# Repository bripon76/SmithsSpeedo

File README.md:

# SmithsSpeedo
 DIY Speedo Conversation from mechanical to electical

# ToDo

- Control and order Top PCB
- Complete, control and order Bottom PCB
- modify Atmel Code for speaking with ESP32 Code

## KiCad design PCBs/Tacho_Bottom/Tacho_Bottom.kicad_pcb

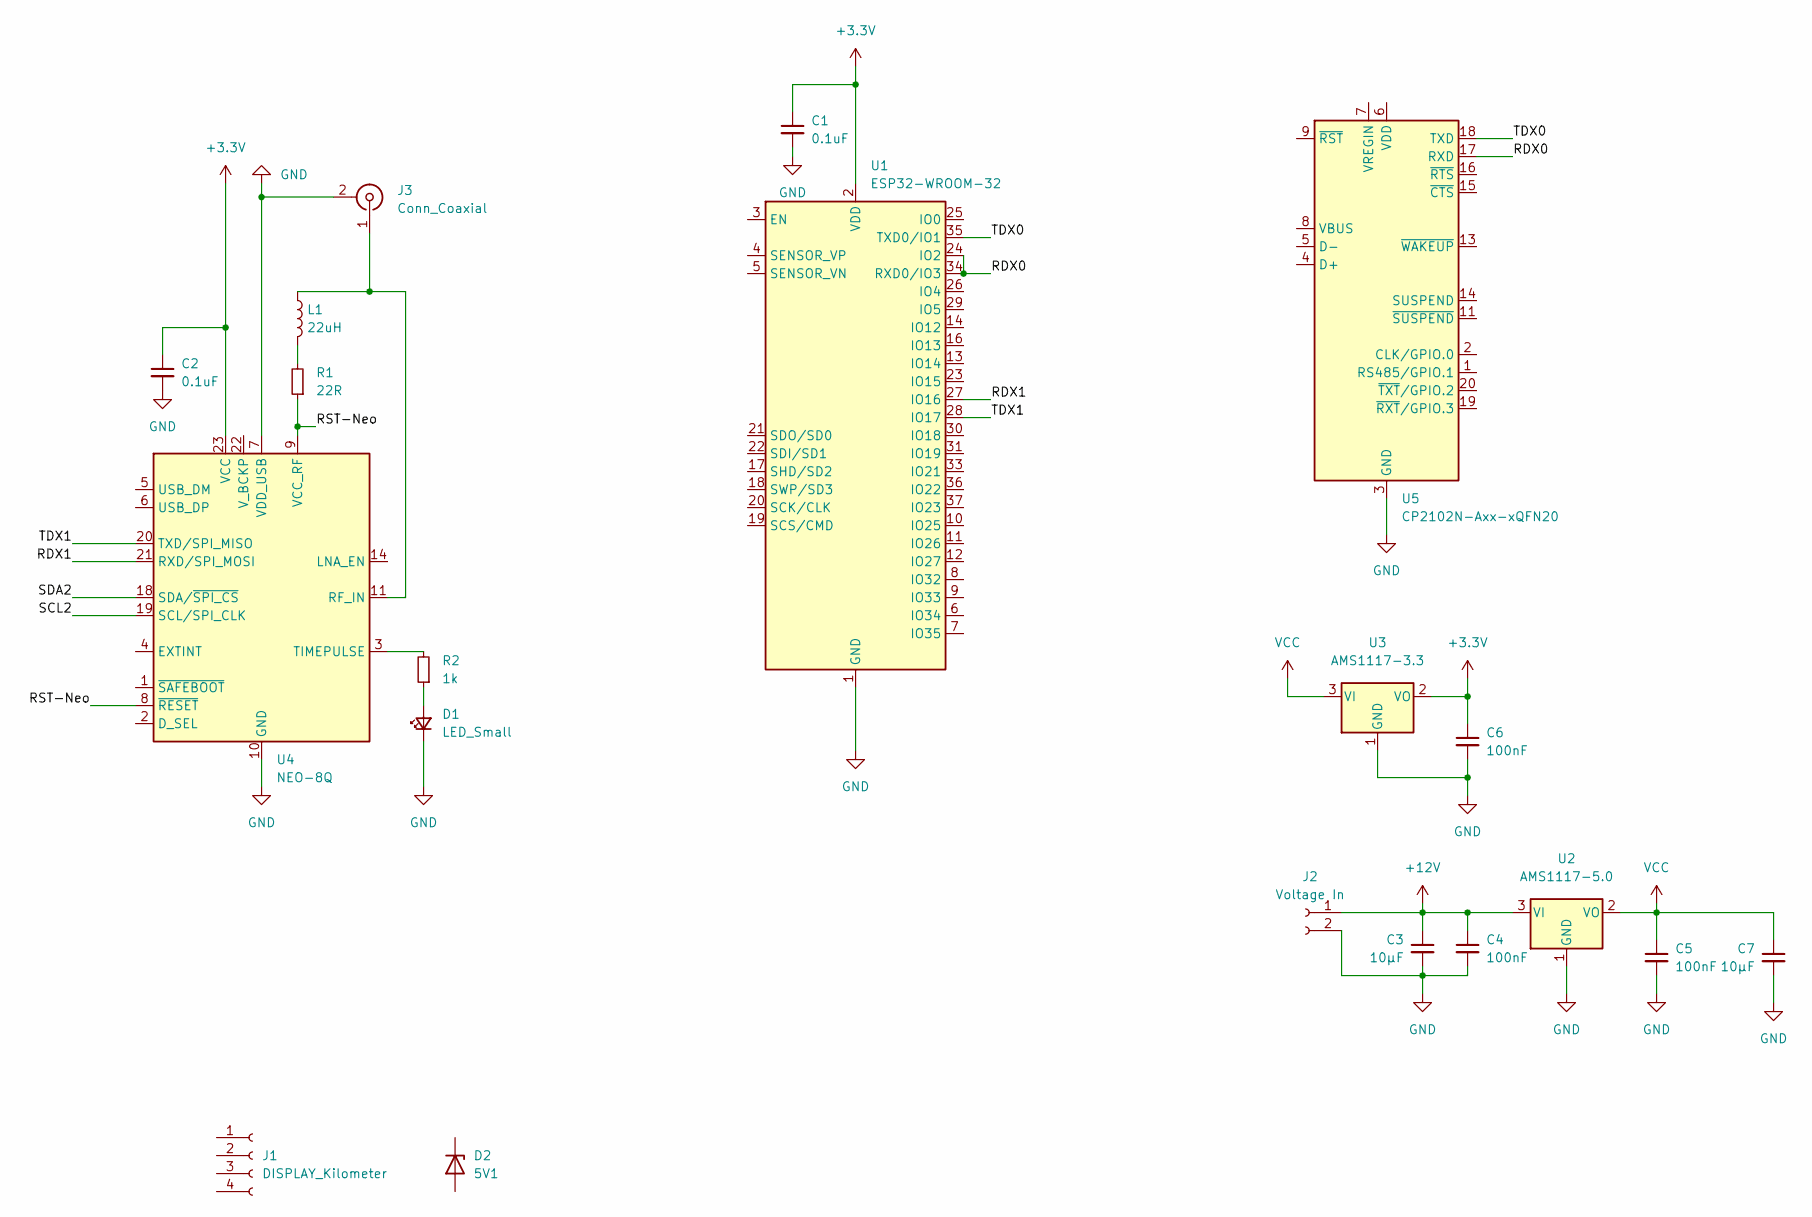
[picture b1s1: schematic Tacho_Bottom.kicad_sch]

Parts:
C1, C2: 0.1uF; C_0603_1608Metric_Pad1.08x0.95mm_HandSolder
C3, C7: 10µF; C_0805_2012Metric_Pad1.18x1.45mm_HandSolder
C4, C5, C6: 100nF; C_0603_1608Metric_Pad1.08x0.95mm_HandSolder
D1: LED_Small; LED_1206_3216Metric_Pad1.42x1.75mm_HandSolder
D2: 5V1; D_SOD-123
J1: DISPLAY_Kilometer; PinHeader_1x04_P2.54mm_Vertical
J2: Voltage In; SolderWire-0.5sqmm_1x02_P4.8mm_D0.9mm_OD2.3mm
J3: Conn_Coaxial; U.FL_Molex_MCRF_73412-0110_Vertical
L1: 22uH; L_12x12mm_H8mm
R1: 22R; R_0603_1608Metric_Pad0.98x0.95mm_HandSolder
R2: 1k; R_0603_1608Metric_Pad0.98x0.95mm_HandSolder
U1: ESP32-WROOM-32
U2: AMS1117-5.0; SOT-223-3_TabPin2
U3: AMS1117-3.3; SOT-223-3_TabPin2
U4: NEO-8Q; ublox_NEO
U5: CP2102N-Axx-xQFN20; SiliconLabs_QFN-20-1EP_3x3mm_P0.5mm

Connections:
+3.3V: C1.1, C2.1, C6.1, U1.2 (VDD), U3.2 (VO), U4.23 (VCC)
+12V: C3.1, C4.1, J2.1, U2.3 (VI)
/RDX0: U1.24 (IO2), U1.34 (RXD0/IO3), U5.17 (RXD)
/RDX1: U1.27 (IO16), U4.21 (RXD/SPI_MOSI)
/RST-Neo: R1.1, U4.8 (~RESET), U4.9 (VCC_RF)
/SCL2: U4.19 (SCL/SPI_CLK)
/SDA2: U4.18 (SDA/~SPI_CS)
/TDX0: U1.35 (TXD0/IO1), U5.18 (TXD)
/TDX1: U1.28 (IO17), U4.20 (TXD/SPI_MISO)
GND: C1.2, C2.2, C3.2, C4.2, C5.2, C6.2, C7.2, D1.1 (K), J2.2, J3.2 (Ext), U1.1 (GND), U1.15 (GND), U1.38 (GND), U1.39 (GND), U2.1 (GND), U3.1 (GND), U4.7 (VDD_USB), U4.10 (GND), U4.12 (GND), U4.13 (GND), U4.24 (GND), U5.3 (GND), U5.12 (GND), U5.21 (GND)
unnamed: D1.2 (A), R2.1
unnamed: J3.1 (In), L1.1, U4.11 (RF_IN)
unnamed: L1.2, R1.2
unnamed: R2.2, U4.3 (TIMEPULSE)
VCC: C5.1, C7.1, U2.2 (VO), U3.3 (VI)

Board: 2 copper layers, 19 parts (2 on the bottom side), 12 nets, no tracks yet.

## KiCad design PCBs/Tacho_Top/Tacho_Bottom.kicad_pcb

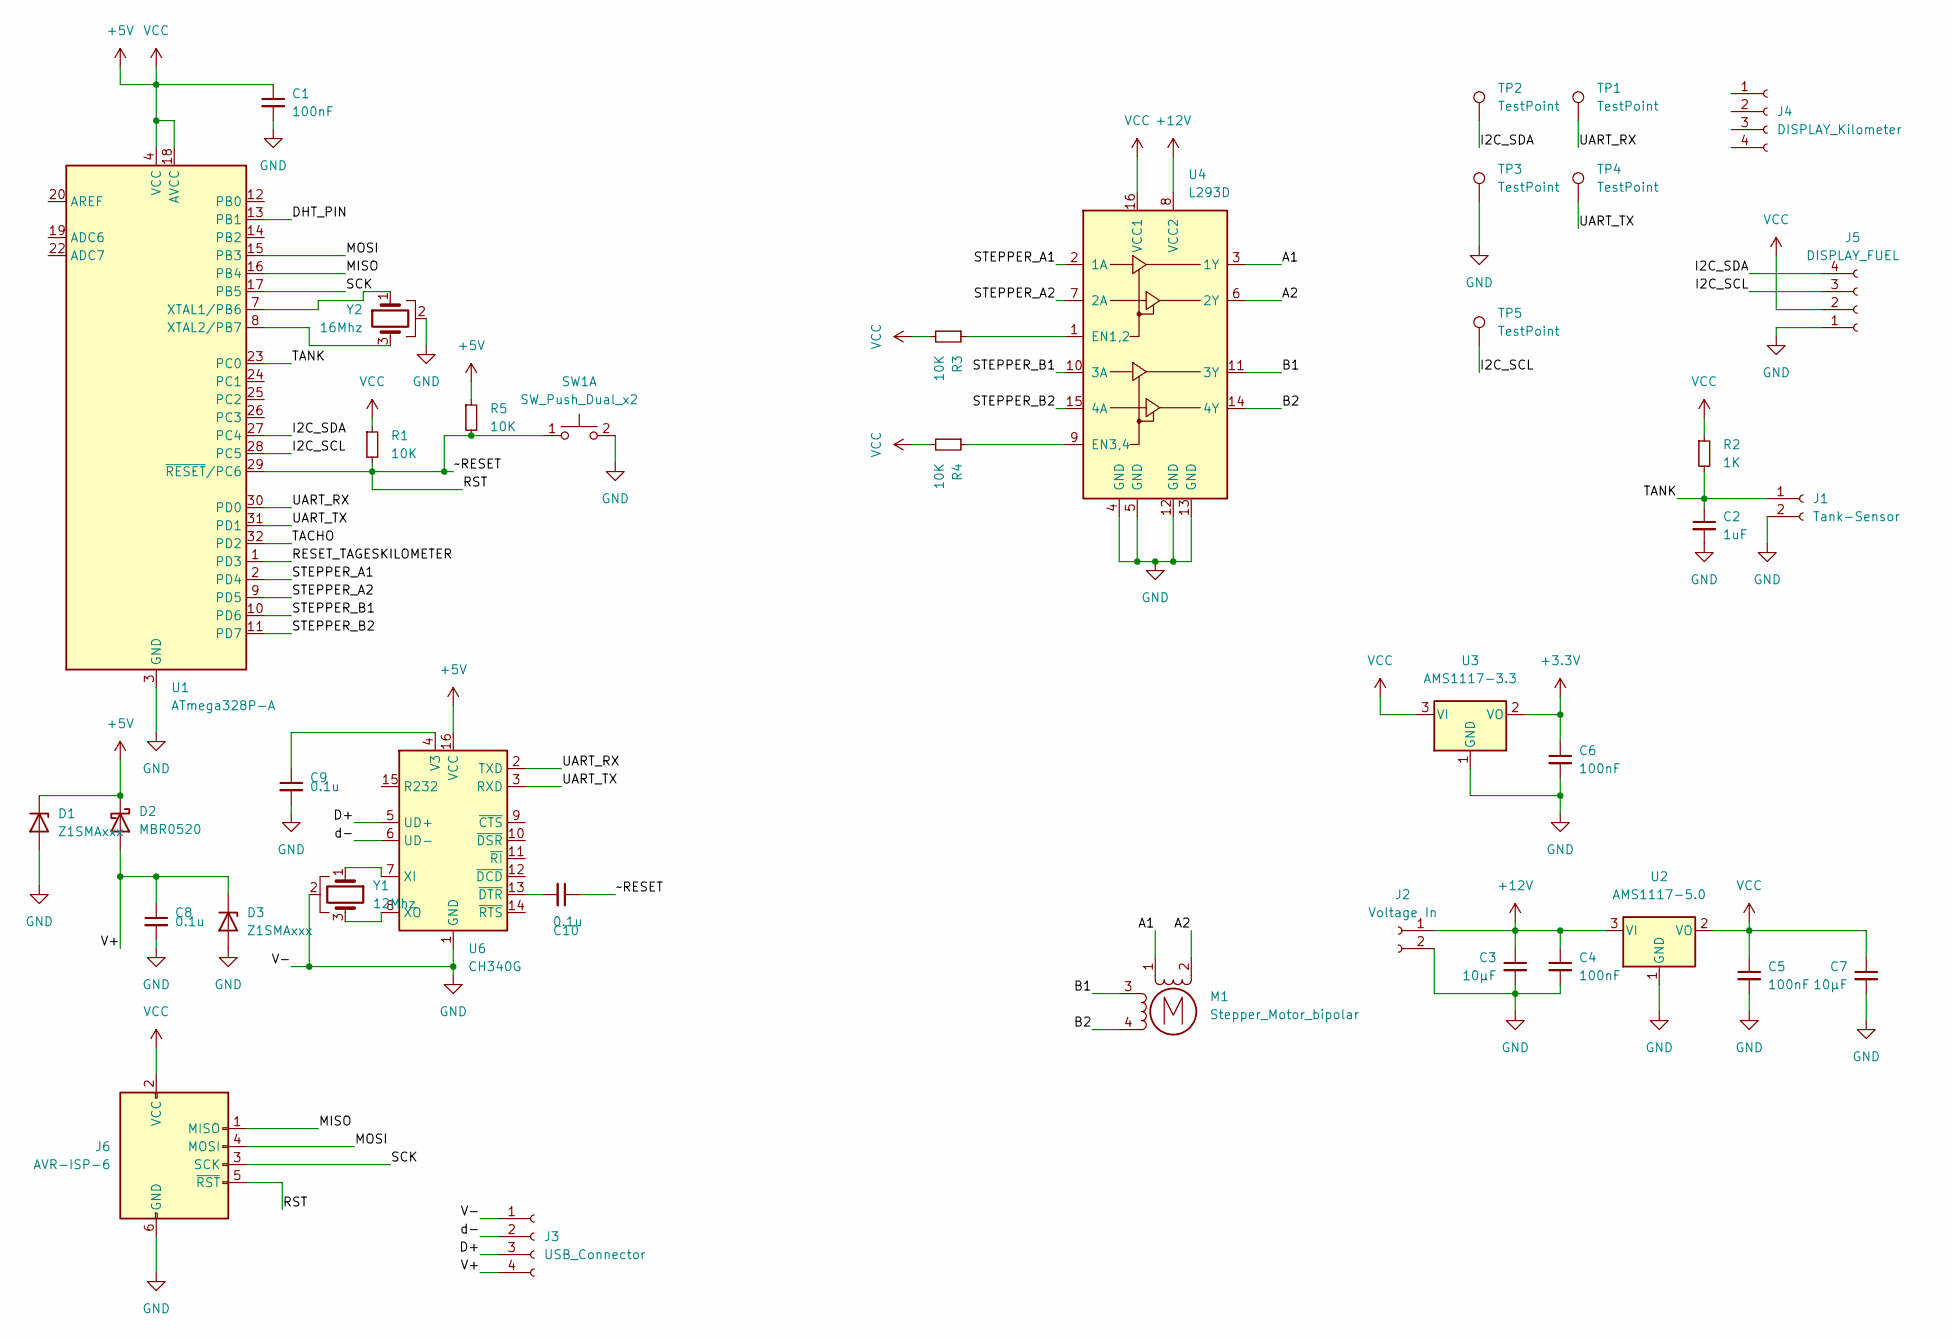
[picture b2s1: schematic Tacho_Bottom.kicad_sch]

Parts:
C1, C4, C5, C6: 100nF; C_0603_1608Metric_Pad1.08x0.95mm_HandSolder
C2: 1uF; R_0603_1608Metric_Pad0.98x0.95mm_HandSolder
C3, C7: 10µF; C_0805_2012Metric_Pad1.18x1.45mm_HandSolder
C8, C9, C10: 0.1u; R_0603_1608Metric_Pad0.98x0.95mm_HandSolder
D1, D3: Z1SMAxxx; D_SMA
D2: MBR0520; D_SOD-123
J1: Tank-Sensor; SolderWire-0.1sqmm_1x02_P3.6mm_D0.4mm_OD1mm
J2: Voltage In; SolderWire-0.5sqmm_1x02_P4.8mm_D0.9mm_OD2.3mm
J3: USB_Connector; PinHeader_1x04_P2.54mm_Vertical
J4: DISPLAY_Kilometer; PinHeader_1x04_P2.54mm_Vertical
J5: DISPLAY_FUEL; SolderWire-0.1sqmm_1x04_P3.6mm_D0.4mm_OD1mm
J6: AVR-ISP-6; PinHeader_2x03_P2.54mm_Vertical
M1: Stepper_Motor_bipolar; X27-168
R1, R3, R4, R5: 10K; R_0603_1608Metric_Pad0.98x0.95mm_HandSolder
R2: 1K; R_0603_1608Metric_Pad0.98x0.95mm_HandSolder
SW1: SW_Push_Dual_x2
TP1, TP2, TP3, TP4, TP5: TestPoint; TestPoint_Pad_D2.0mm
U1: ATmega328P-A; TQFP-32_7x7mm_P0.8mm
U2: AMS1117-5.0; SOT-223-3_TabPin2
U3: AMS1117-3.3; SOT-223-3_TabPin2
U4: L293D; DIP-16_W7.62mm
U6: CH340G; SOIC-16_3.9x9.9mm_P1.27mm
Y1: 12Mhz
Y2: 16Mhz

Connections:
+3.3V: C6.1, U3.2 (VO)
+5V: C1.1, C5.1, C7.1, D1.1 (K), D2.1 (K), J5.2, J6.2 (VCC), R1.1, R2.1, R3.2, R4.2, R5.1, U1.4 (VCC), U1.6 (VCC), U1.18 (AVCC), U2.2 (VO), U3.3 (VI), U4.16 (VCC1), U6.16 (VCC)
+12V: C3.1, C4.1, J2.1, U2.3 (VI), U4.8 (VCC2)
/A1: M1.1, U4.3 (1Y)
/A2: M1.2 (-), U4.6 (2Y)
/B1: M1.3, U4.11 (3Y)
/B2: M1.4, U4.14 (4Y)
/D+: J3.3, U6.5 (UD+)
/DHT_PIN: U1.13 (PB1)
/I2C_SCL: J5.3, TP5.1, U1.28 (PC5)
/I2C_SDA: J5.4, TP2.1, U1.27 (PC4)
/MISO: J6.1 (MISO), U1.16 (PB4)
/MOSI: J6.4 (MOSI), U1.15 (PB3)
/RESET_TAGESKILOMETER: U1.1 (PD3)
/RST: C10.1, J6.5 (~RST), R1.2, R5.2, SW1.1 (C), U1.29 (~RESET/PC6)
/SCK: J6.3 (SCK), U1.17 (PB5)
/STEPPER_A1: U1.2 (PD4), U4.2 (1A)
/STEPPER_A2: U1.9 (PD5), U4.7 (2A)
/STEPPER_B1: U1.10 (PD6), U4.10 (3A)
/STEPPER_B2: U1.11 (PD7), U4.15 (4A)
/TACHO: U1.32 (PD2)
/TANK: C2.1, J1.1, R2.2, U1.23 (PC0)
/UART_RX: TP1.1, U1.30 (PD0), U6.2 (TXD)
/UART_TX: TP4.1, U1.31 (PD1), U6.3 (RXD)
/V+: C8.1, D2.2 (A), D3.1 (K), J3.4
/d-: J3.2, U6.6 (UD-)
GND: C1.2, C2.2, C3.2, C4.2, C5.2, C6.2, C7.2, C8.2, C9.2, D1.2 (A), D3.2 (A), J1.2, J2.2, J3.1, J5.1, J6.6 (GND), SW1.2 (D), TP3.1, U1.3 (GND), U1.5 (GND), U1.21 (GND), U2.1 (GND), U3.1 (GND), U4.4 (GND), U4.5 (GND), U4.12 (GND), U4.13 (GND), U6.1 (GND), Y1.2, Y2.2
unnamed: C9.1, U6.4 (V3)
unnamed: C10.2, U6.13 (~DTR)
unnamed: R3.1, U4.1 (EN1,2)
unnamed: R4.1, U4.9 (EN3,4)
unnamed: U1.7 (XTAL1/PB6), Y2.1
unnamed: U1.8 (XTAL2/PB7), Y2.3
unnamed: U6.7 (XI), Y1.1
unnamed: U6.8 (XO), Y1.3

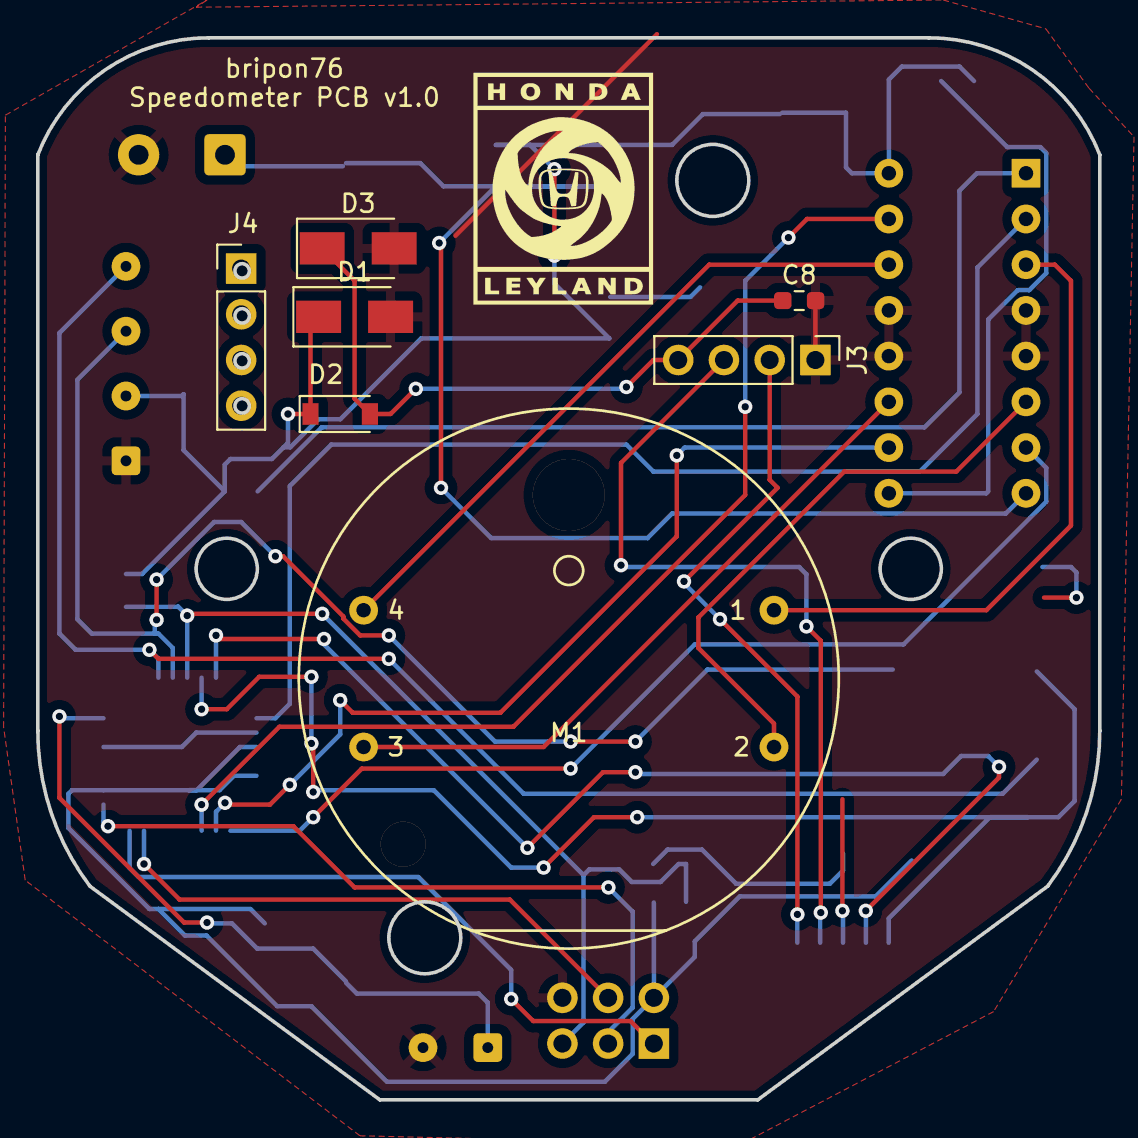
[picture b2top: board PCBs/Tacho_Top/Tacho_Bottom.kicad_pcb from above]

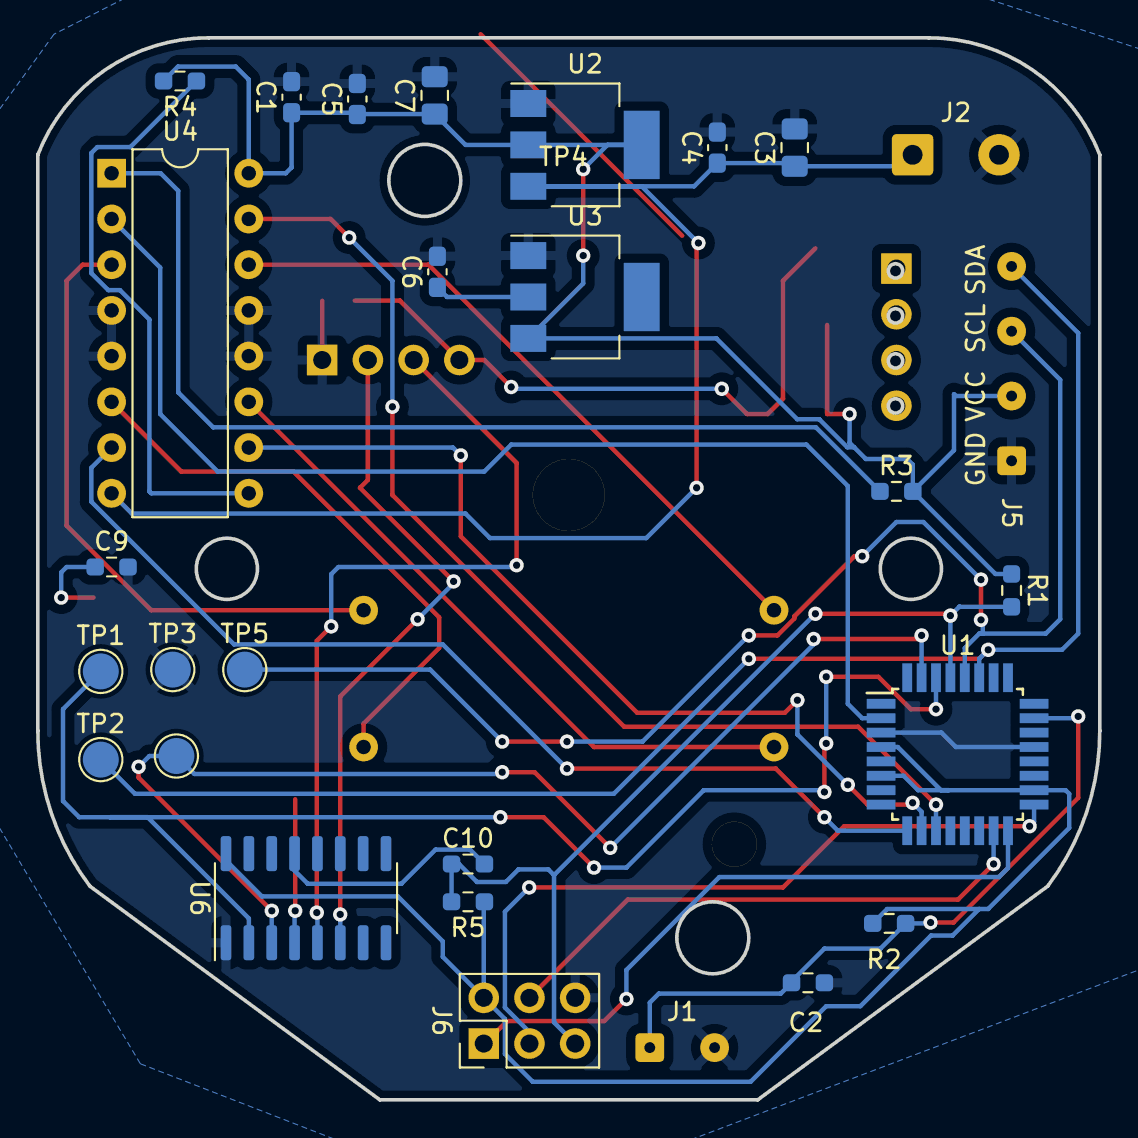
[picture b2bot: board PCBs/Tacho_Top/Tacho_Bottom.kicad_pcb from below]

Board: 2 copper layers, 59.0 x 59.0 mm, 35 parts (28 on the bottom side), 28 nets.

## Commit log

2023-01-18 new Version
    new Version
